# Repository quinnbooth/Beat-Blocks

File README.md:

# Beat-Blocks
Analog drum kit controlled by a sequencer. Theremin module for bassline.

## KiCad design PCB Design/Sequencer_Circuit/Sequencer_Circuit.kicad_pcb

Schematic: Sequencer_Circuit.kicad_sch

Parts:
5V_POWER1: Barrel_Jack_Switch; BARREL_JACK
555_TIMER1: LM555CN; DIP-8_W7.62mm
ALT_POWER1: Conn_01x02_Pin; OUTPUT_PINS_2
BEATS_1_1, BEATS_1_2, BEATS_1_3, BEATS_1_4, BEATS_2_1, BEATS_2_2, BEATS_2_3, BEATS_2_4, BEATS_3_1, BEATS_3_2, BEATS_3_3, BEATS_3_4: DM74LS54N
C1, C2, C3: C; C_Disc_D5.1mm_W3.2mm_P5.00mm
COMBINE_1, COMBINE_2, COMBINE_3: MC14012B
DISABLER1: GANGED_SW_SP3T; GANGED_SWITCH
D_1_1_1, D_1_1_2, D_1_2_1, D_1_2_2, D_1_3_1, D_1_3_2, D_1_4_1, D_1_4_2, D_1_5_1, D_1_5_2, D_1_6_1, D_1_6_2, D_1_7_1, D_1_7_2, D_1_8_1, D_1_8_2, D_2_1_1, D_2_1_2, D_2_2_1, D_2_2_2, D_2_3_1, D_2_3_2, D_2_4_1, D_2_4_2, D_2_5_1, D_2_5_2, D_2_6_1, D_2_6_2, D_2_7_1, D_2_7_2, D_2_8_1, D_2_8_2, D_3_1_1, D_3_1_2, D_3_2_1, D_3_2_2, D_3_3_1, D_3_3_2, D_3_4_1, D_3_4_2, D_3_5_1, D_3_5_2, D_3_6_1, D_3_6_2, D_3_7_1, D_3_7_2, D_3_8_1, D_3_8_2: LED; D_5W_P5.08mm_Vertical_AnodeUp
INVERT1: DM74LS04N
JK_1_1, JK_1_2, JK_1_3, JK_1_4, JK_1_5, JK_1_6, JK_1_7, JK_1_8, JK_2_1, JK_2_2, JK_2_3, JK_2_4, JK_2_5, JK_2_6, JK_2_7, JK_2_8, JK_3_1, JK_3_2, JK_3_3, JK_3_4, JK_3_5, JK_3_6, JK_3_7, JK_3_8: SN74107N; MPN SN74107N
ONE_SHOT1: SN74LS95BN
OUT_PINS1: OUT_PINS; OUTPUT_PINS_5
R1, R2: R; R_Axial_DIN0309_L9.0mm_D3.2mm_P12.70mm_Horizontal
R3: 1M; R_Axial_DIN0309_L9.0mm_D3.2mm_P12.70mm_Horizontal
R4: 100K; R_Axial_DIN0309_L9.0mm_D3.2mm_P12.70mm_Horizontal
R_1_1_1, R_1_1_2, R_1_2_1, R_1_2_2, R_1_3_1, R_1_3_2, R_1_4_1, R_1_4_2, R_1_5_1, R_1_5_2, R_1_6_1, R_1_6_2, R_1_7_1, R_1_7_2, R_1_8_1, R_1_8_2, R_2_1_1, R_2_1_2, R_2_2_1, R_2_2_2, R_2_3_1, R_2_3_2, R_2_4_1, R_2_4_2, R_2_5_1, R_2_5_2, R_2_6_1, R_2_6_2, R_2_7_1, R_2_7_2, R_2_8_1, R_2_8_2, R_3_1_1, R_3_1_2, R_3_2_1, R_3_2_2, R_3_3_1, R_3_3_2, R_3_4_1, R_3_4_2, R_3_5_1, R_3_5_2, R_3_6_1, R_3_6_2, R_3_7_1, R_3_7_2, R_3_8_1, R_3_8_2: R; R_Axial_DIN0309_L9.0mm_D3.2mm_P12.70mm_Horizontal
R_Tempo1: 2M; Potentiometer_Omeg_PC16BU_Vertical
SHIFT_1, SHIFT_2: DM74164N
SW1, SW2, SW3, SW4, SW5, SW6, SW7, SW8, SW9, SW10, SW11, SW12, SW13, SW14, SW15, SW16: ARCADE_BUTTON
SW1_C1, SW2_C1, SW3_C1, SW4_C1, SW5_C1, SW6_C1, SW7_C1, SW8_C1, SW9_C1, SW10_C1, SW11_C1, SW12_C1, SW13_C1, SW14_C1, SW15_C1, SW16_C1: C; C_Disc_D5.1mm_W3.2mm_P5.00mm
SW1_R1, SW1_R2, SW2_R1, SW2_R2, SW3_R1, SW3_R2, SW4_R1, SW4_R2, SW5_R1, SW5_R2, SW6_R1, SW6_R2, SW7_R1, SW7_R2, SW8_R1, SW8_R2, SW9_R1, SW9_R2, SW10_R1, SW10_R2, SW11_R1, SW11_R2, SW12_R1, SW12_R2, SW13_R1, SW13_R2, SW14_R1, SW14_R2, SW15_R1, SW15_R2, SW16_R1, SW16_R2: R; R_Axial_DIN0309_L9.0mm_D3.2mm_P12.70mm_Horizontal
XOR1: CD4070BE

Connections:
+5V: 5V_POWER1.1, 555_TIMER1.4 (R), 555_TIMER1.8 (VCC), ALT_POWER1.1, BEATS_1_1.5 (E), BEATS_1_1.9 (F), BEATS_1_1.14 (VCC), BEATS_1_2.5 (E), BEATS_1_2.9 (F), BEATS_1_2.14 (VCC), BEATS_1_3.5 (E), BEATS_1_3.9 (F), BEATS_1_3.14 (VCC), BEATS_1_4.5 (E), BEATS_1_4.9 (F), BEATS_1_4.14 (VCC), BEATS_2_1.5 (E), BEATS_2_1.9 (F), BEATS_2_1.14 (VCC), BEATS_2_2.5 (E), BEATS_2_2.9 (F), BEATS_2_2.14 (VCC), BEATS_2_3.5 (E), BEATS_2_3.9 (F), BEATS_2_3.14 (VCC), BEATS_2_4.5 (E), BEATS_2_4.9 (F), BEATS_2_4.14 (VCC), BEATS_3_1.5 (E), BEATS_3_1.9 (F), BEATS_3_1.14 (VCC), BEATS_3_2.5 (E), BEATS_3_2.9 (F), BEATS_3_2.14 (VCC), BEATS_3_3.5 (E), BEATS_3_3.9 (F), BEATS_3_3.14 (VCC), BEATS_3_4.5 (E), BEATS_3_4.9 (F), BEATS_3_4.14 (VCC), C3.1, COMBINE_1.11 (IN_3_B), COMBINE_1.12 (IN_4_B), COMBINE_1.14 (VDD), COMBINE_2.11 (IN_3_B), COMBINE_2.12 (IN_4_B), COMBINE_2.14 (VDD), COMBINE_3.11 (IN_3_B), COMBINE_3.12 (IN_4_B), COMBINE_3.14 (VDD), INVERT1.14 (VCC), JK_1_1.10 (2~CLR), JK_1_1.13 (1~CLR), JK_1_1.14 (VCC), JK_1_2.10 (2~CLR), JK_1_2.13 (1~CLR), JK_1_2.14 (VCC), JK_1_3.10 (2~CLR), JK_1_3.13 (1~CLR), JK_1_3.14 (VCC), JK_1_4.10 (2~CLR), JK_1_4.13 (1~CLR), JK_1_4.14 (VCC), JK_1_5.10 (2~CLR), JK_1_5.13 (1~CLR), JK_1_5.14 (VCC), JK_1_6.10 (2~CLR), JK_1_6.13 (1~CLR), JK_1_6.14 (VCC), JK_1_7.10 (2~CLR), JK_1_7.13 (1~CLR), JK_1_7.14 (VCC), JK_1_8.10 (2~CLR), JK_1_8.13 (1~CLR), JK_1_8.14 (VCC), JK_2_1.10 (2~CLR), JK_2_1.13 (1~CLR), JK_2_1.14 (VCC), JK_2_2.10 (2~CLR), JK_2_2.13 (1~CLR), JK_2_2.14 (VCC), JK_2_3.10 (2~CLR), JK_2_3.13 (1~CLR), JK_2_3.14 (VCC), JK_2_4.10 (2~CLR), JK_2_4.13 (1~CLR), JK_2_4.14 (VCC), JK_2_5.10 (2~CLR), JK_2_5.13 (1~CLR), JK_2_5.14 (VCC), JK_2_6.10 (2~CLR), JK_2_6.13 (1~CLR), JK_2_6.14 (VCC), JK_2_7.10 (2~CLR), JK_2_7.13 (1~CLR), JK_2_7.14 (VCC), JK_2_8.10 (2~CLR), JK_2_8.13 (1~CLR), JK_2_8.14 (VCC), JK_3_1.10 (2~CLR), JK_3_1.13 (1~CLR), JK_3_1.14 (VCC), JK_3_2.10 (2~CLR), JK_3_2.13 (1~CLR), JK_3_2.14 (VCC), JK_3_3.10 (2~CLR), JK_3_3.13 (1~CLR), JK_3_3.14 (VCC), JK_3_4.10 (2~CLR), JK_3_4.13 (1~CLR), JK_3_4.14 (VCC), JK_3_5.10 (2~CLR), JK_3_5.13 (1~CLR), JK_3_5.14 (VCC), JK_3_6.10 (2~CLR), JK_3_6.13 (1~CLR), JK_3_6.14 (VCC), JK_3_7.10 (2~CLR), JK_3_7.13 (1~CLR), JK_3_7.14 (VCC), JK_3_8.10 (2~CLR), JK_3_8.13 (1~CLR), JK_3_8.14 (VCC), ONE_SHOT1.14 (VCC), R2.1, R3.2, SHIFT_1.2 (B), SHIFT_1.9 (CLR), SHIFT_1.14 (VCC), SHIFT_2.2 (B), SHIFT_2.9 (CLR), SHIFT_2.14 (VCC), SW1_R2.1, SW2_R2.2, SW3_R2.1, SW4_R2.2, SW5_R2.1, SW6_R2.2, SW7_R2.1, SW8_R2.2, SW9_R2.1, SW10_R2.2, SW11_R2.1, SW12_R2.2, SW13_R2.1, SW14_R2.2, SW15_R2.1, SW16_R2.2, XOR1.14 (VDD)
GND: 5V_POWER1.2, 5V_POWER1.3, 555_TIMER1.1 (GND), ALT_POWER1.2, BEATS_1_1.7 (GND), BEATS_1_2.7 (GND), BEATS_1_3.7 (GND), BEATS_1_4.7 (GND), BEATS_2_1.7 (GND), BEATS_2_2.7 (GND), BEATS_2_3.7 (GND), BEATS_2_4.7 (GND), BEATS_3_1.7 (GND), BEATS_3_2.7 (GND), BEATS_3_3.7 (GND), BEATS_3_4.7 (GND), C1.1, C2.2, C3.2, COMBINE_1.7 (VSS), COMBINE_2.7 (VSS), COMBINE_3.7 (VSS), DISABLER1.7, DISABLER1.8 (7), INVERT1.7 (GND), JK_1_1.7 (GND), JK_1_2.7 (GND), JK_1_3.7 (GND), JK_1_4.7 (GND), JK_1_5.7 (GND), JK_1_6.7 (GND), JK_1_7.7 (GND), JK_1_8.7 (GND), JK_2_1.7 (GND), JK_2_2.7 (GND), JK_2_3.7 (GND), JK_2_4.7 (GND), JK_2_5.7 (GND), JK_2_6.7 (GND), JK_2_7.7 (GND), JK_2_8.7 (GND), JK_3_1.7 (GND), JK_3_2.7 (GND), JK_3_3.7 (GND), JK_3_4.7 (GND), JK_3_5.7 (GND), JK_3_6.7 (GND), JK_3_7.7 (GND), JK_3_8.7 (GND), ONE_SHOT1.1 (SER), ONE_SHOT1.6 (MODE), ONE_SHOT1.7 (GND), OUT_PINS1.1, R4.2, R_1_1_1.1, R_1_1_2.1, R_1_2_1.1, R_1_2_2.1, R_1_3_1.1, R_1_3_2.1, R_1_4_1.1, R_1_4_2.1, R_1_5_1.1, R_1_5_2.1, R_1_6_1.1, R_1_6_2.1, R_1_7_1.1, R_1_7_2.1, R_1_8_1.1, R_1_8_2.1, R_2_1_1.1, R_2_1_2.1, R_2_2_1.1, R_2_2_2.1, R_2_3_1.1, R_2_3_2.1, R_2_4_1.1, R_2_4_2.1, R_2_5_1.1, R_2_5_2.1, R_2_6_1.1, R_2_6_2.1, R_2_7_1.1, R_2_7_2.1, R_2_8_1.1, R_2_8_2.1, R_3_1_1.1, R_3_1_2.1, R_3_2_1.1, R_3_2_2.1, R_3_3_1.1, R_3_3_2.1, R_3_4_1.1, R_3_4_2.1, R_3_5_1.1, R_3_5_2.1, R_3_6_1.1, R_3_6_2.1, R_3_7_1.1, R_3_7_2.1, R_3_8_1.1, R_3_8_2.1, SHIFT_1.7 (GND), SHIFT_2.7 (GND), SW1.2, SW1_C1.2, SW1_R1.1, SW2.2, SW2_C1.2, SW2_R1.1, SW3.2, SW3_C1.2, SW3_R1.1, SW4.2, SW4_C1.2, SW4_R1.1, SW5.2, SW5_C1.2, SW5_R1.1, SW6.2, SW6_C1.2, SW6_R1.1, SW7.2, SW7_C1.2, SW7_R1.1, SW8.2, SW8_C1.2, SW8_R1.1, SW9.2, SW9_C1.2, SW9_R1.1, SW10.2, SW10_C1.2, SW10_R1.1, SW11.2, SW11_C1.2, SW11_R1.1, SW12.2, SW12_C1.2, SW12_R1.1, SW13.2, SW13_C1.2, SW13_R1.1, SW14.2, SW14_C1.2, SW14_R1.1, SW15.2, SW15_C1.2, SW15_R1.1, SW16.2, SW16_C1.2, SW16_R1.1, XOR1.5 (C), XOR1.7 (GND)
unnamed: 555_TIMER1.5 (CV), C1.2
unnamed: 555_TIMER1.7 (DIS), R1.2, R2.2
unnamed: 555_TIMER1.3 (Q), COMBINE_1.9 (IN_1_B), COMBINE_2.9 (IN_1_B), COMBINE_3.9 (IN_1_B), ONE_SHOT1.9 (CLK1), SHIFT_1.8 (CLK), SHIFT_2.8 (CLK)
unnamed: 555_TIMER1.2 (TR), 555_TIMER1.6 (THR), C2.1, R_Tempo1.1, R_Tempo1.2
unnamed: BEATS_1_1.1 (A), D_1_1_1.2 (A), JK_1_1.3 (1Q)
unnamed: BEATS_1_1.2 (B), BEATS_2_1.2 (B), BEATS_3_1.2 (B), SHIFT_1.3 (Q_A), SW1.3
unnamed: BEATS_1_1.3 (C), D_1_1_2.2 (A), JK_1_1.5 (2Q)
unnamed: BEATS_1_1.4 (D), BEATS_2_1.4 (D), BEATS_3_1.4 (D), SHIFT_1.4 (Q_B), SW2.3
unnamed: BEATS_1_1.10 (G), BEATS_2_1.10 (G), BEATS_3_1.10 (G), SHIFT_1.6 (Q_D), SW4.3
unnamed: BEATS_1_1.11 (H), D_1_2_2.2 (A), JK_1_2.5 (2Q)
unnamed: BEATS_1_1.12 (I), BEATS_2_1.12 (I), BEATS_3_1.12 (I), SHIFT_1.5 (Q_C), SW3.3
unnamed: BEATS_1_1.13 (J), D_1_2_1.2 (A), JK_1_2.3 (1Q)
unnamed: BEATS_1_1.6 (Y), COMBINE_1.2 (IN_1_A)
unnamed: BEATS_1_2.1 (A), D_1_3_1.2 (A), JK_1_3.3 (1Q)
unnamed: BEATS_1_2.2 (B), BEATS_2_2.2 (B), BEATS_3_2.2 (B), SHIFT_1.10 (Q_E), SW5.3
unnamed: BEATS_1_2.3 (C), D_1_3_2.2 (A), JK_1_3.5 (2Q)
unnamed: BEATS_1_2.4 (D), BEATS_2_2.4 (D), BEATS_3_2.4 (D), SHIFT_1.11 (Q_F), SW6.3
unnamed: BEATS_1_2.10 (G), BEATS_2_2.10 (G), BEATS_3_2.10 (G), SHIFT_1.13 (Q_H), SW8.3, XOR1.6 (D)
unnamed: BEATS_1_2.11 (H), D_1_4_2.2 (A), JK_1_4.5 (2Q)
unnamed: BEATS_1_2.12 (I), BEATS_2_2.12 (I), BEATS_3_2.12 (I), SHIFT_1.12 (Q_G), SW7.3
unnamed: BEATS_1_2.13 (J), D_1_4_1.2 (A), JK_1_4.3 (1Q)
unnamed: BEATS_1_2.6 (Y), COMBINE_1.3 (IN_2_A)
unnamed: BEATS_1_3.1 (A), D_1_5_1.2 (A), JK_1_5.3 (1Q)
unnamed: BEATS_1_3.2 (B), BEATS_2_3.2 (B), BEATS_3_3.2 (B), SHIFT_2.3 (Q_A), SW9.3
unnamed: BEATS_1_3.3 (C), D_1_5_2.2 (A), JK_1_5.5 (2Q)
unnamed: BEATS_1_3.4 (D), BEATS_2_3.4 (D), BEATS_3_3.4 (D), SHIFT_2.4 (Q_B), SW10.3
unnamed: BEATS_1_3.10 (G), BEATS_2_3.10 (G), BEATS_3_3.10 (G), SHIFT_2.6 (Q_D), SW12.3
unnamed: BEATS_1_3.11 (H), D_1_6_2.2 (A), JK_1_6.5 (2Q)
unnamed: BEATS_1_3.12 (I), BEATS_2_3.12 (I), BEATS_3_3.12 (I), SHIFT_2.5 (Q_C), SW11.3
unnamed: BEATS_1_3.13 (J), D_1_6_1.2 (A), JK_1_6.3 (1Q)
unnamed: BEATS_1_3.6 (Y), COMBINE_1.4 (IN_3_A)
unnamed: BEATS_1_4.1 (A), D_1_7_1.2 (A), JK_1_7.3 (1Q)
unnamed: BEATS_1_4.2 (B), BEATS_2_4.2 (B), BEATS_3_4.2 (B), SHIFT_2.10 (Q_E), SW13.3
unnamed: BEATS_1_4.3 (C), D_1_7_2.2 (A), JK_1_7.5 (2Q)
unnamed: BEATS_1_4.4 (D), BEATS_2_4.4 (D), BEATS_3_4.4 (D), SHIFT_2.11 (Q_F), SW14.3
unnamed: BEATS_1_4.10 (G), BEATS_2_4.10 (G), BEATS_3_4.10 (G), SHIFT_2.13 (Q_H), SW16.3, XOR1.13 (H)
unnamed: BEATS_1_4.11 (H), D_1_8_2.2 (A), JK_1_8.5 (2Q)
unnamed: BEATS_1_4.12 (I), BEATS_2_4.12 (I), BEATS_3_4.12 (I), SHIFT_2.12 (Q_G), SW15.3
unnamed: BEATS_1_4.13 (J), D_1_8_1.2 (A), JK_1_8.3 (1Q)
unnamed: BEATS_1_4.6 (Y), COMBINE_1.5 (IN_4_A)
unnamed: BEATS_2_1.1 (A), D_2_1_1.2 (A), JK_2_1.3 (1Q)
unnamed: BEATS_2_1.3 (C), D_2_1_2.2 (A), JK_2_1.5 (2Q)
unnamed: BEATS_2_1.11 (H), D_2_2_2.2 (A), JK_2_2.5 (2Q)
unnamed: BEATS_2_1.13 (J), D_2_2_1.2 (A), JK_2_2.3 (1Q)
unnamed: BEATS_2_1.6 (Y), COMBINE_2.2 (IN_1_A)
unnamed: BEATS_2_2.1 (A), D_2_3_1.2 (A), JK_2_3.3 (1Q)
unnamed: BEATS_2_2.3 (C), D_2_3_2.2 (A), JK_2_3.5 (2Q)
unnamed: BEATS_2_2.11 (H), D_2_4_2.2 (A), JK_2_4.5 (2Q)
unnamed: BEATS_2_2.13 (J), D_2_4_1.2 (A), JK_2_4.3 (1Q)
unnamed: BEATS_2_2.6 (Y), COMBINE_2.3 (IN_2_A)
unnamed: BEATS_2_3.1 (A), D_2_5_1.2 (A), JK_2_5.3 (1Q)
unnamed: BEATS_2_3.3 (C), D_2_5_2.2 (A), JK_2_5.5 (2Q)
unnamed: BEATS_2_3.11 (H), D_2_6_2.2 (A), JK_2_6.5 (2Q)
unnamed: BEATS_2_3.13 (J), D_2_6_1.2 (A), JK_2_6.3 (1Q)
unnamed: BEATS_2_3.6 (Y), COMBINE_2.4 (IN_3_A)
unnamed: BEATS_2_4.1 (A), D_2_7_1.2 (A), JK_2_7.3 (1Q)
unnamed: BEATS_2_4.3 (C), D_2_7_2.2 (A), JK_2_7.5 (2Q)
unnamed: BEATS_2_4.11 (H), D_2_8_2.2 (A), JK_2_8.5 (2Q)
unnamed: BEATS_2_4.13 (J), D_2_8_1.2 (A), JK_2_8.3 (1Q)
unnamed: BEATS_2_4.6 (Y), COMBINE_2.5 (IN_4_A)
unnamed: BEATS_3_1.1 (A), D_3_1_1.2 (A), JK_3_1.3 (1Q)
unnamed: BEATS_3_1.3 (C), D_3_1_2.2 (A), JK_3_1.5 (2Q)
unnamed: BEATS_3_1.11 (H), D_3_2_2.2 (A), JK_3_2.5 (2Q)
unnamed: BEATS_3_1.13 (J), D_3_2_1.2 (A), JK_3_2.3 (1Q)
unnamed: BEATS_3_1.6 (Y), COMBINE_3.2 (IN_1_A)
unnamed: BEATS_3_2.1 (A), D_3_3_1.2 (A), JK_3_3.3 (1Q)
unnamed: BEATS_3_2.3 (C), D_3_3_2.2 (A), JK_3_3.5 (2Q)
unnamed: BEATS_3_2.11 (H), D_3_4_2.2 (A), JK_3_4.5 (2Q)
unnamed: BEATS_3_2.13 (J), D_3_4_1.2 (A), JK_3_4.3 (1Q)
unnamed: BEATS_3_2.6 (Y), COMBINE_3.3 (IN_2_A)
unnamed: BEATS_3_3.1 (A), D_3_5_1.2 (A), JK_3_5.3 (1Q)
unnamed: BEATS_3_3.3 (C), D_3_5_2.2 (A), JK_3_5.5 (2Q)
unnamed: BEATS_3_3.11 (H), D_3_6_2.2 (A), JK_3_6.5 (2Q)
unnamed: BEATS_3_3.13 (J), D_3_6_1.2 (A), JK_3_6.3 (1Q)
unnamed: BEATS_3_3.6 (Y), COMBINE_3.4 (IN_3_A)
unnamed: BEATS_3_4.1 (A), D_3_7_1.2 (A), JK_3_7.3 (1Q)
unnamed: BEATS_3_4.3 (C), D_3_7_2.2 (A), JK_3_7.5 (2Q)
unnamed: BEATS_3_4.11 (H), D_3_8_2.2 (A), JK_3_8.5 (2Q)
unnamed: BEATS_3_4.13 (J), D_3_8_1.2 (A), JK_3_8.3 (1Q)
unnamed: BEATS_3_4.6 (Y), COMBINE_3.5 (IN_4_A)
unnamed: COMBINE_1.1 (OUT_A), COMBINE_1.10 (IN_2_B)
unnamed: COMBINE_1.13 (OUT_B), INVERT1.1 (A1)
unnamed: COMBINE_2.1 (OUT_A), COMBINE_2.10 (IN_2_B)
unnamed: COMBINE_2.13 (OUT_B), INVERT1.3 (A2)
unnamed: COMBINE_3.1 (OUT_A), COMBINE_3.10 (IN_2_B)
unnamed: COMBINE_3.13 (OUT_B), INVERT1.5 (A3)
unnamed: D_1_1_1.1 (K), R_1_1_1.2
unnamed: D_1_1_2.1 (K), R_1_1_2.2
unnamed: D_1_2_1.1 (K), R_1_2_1.2
unnamed: D_1_2_2.1 (K), R_1_2_2.2
unnamed: D_1_3_1.1 (K), R_1_3_1.2
unnamed: D_1_3_2.1 (K), R_1_3_2.2
unnamed: D_1_4_1.1 (K), R_1_4_1.2
unnamed: D_1_4_2.1 (K), R_1_4_2.2
unnamed: D_1_5_1.1 (K), R_1_5_1.2
unnamed: D_1_5_2.1 (K), R_1_5_2.2
unnamed: D_1_6_1.1 (K), R_1_6_1.2
unnamed: D_1_6_2.1 (K), R_1_6_2.2
unnamed: D_1_7_1.1 (K), R_1_7_1.2
unnamed: D_1_7_2.1 (K), R_1_7_2.2
unnamed: D_1_8_1.1 (K), R_1_8_1.2
unnamed: D_1_8_2.1 (K), R_1_8_2.2
unnamed: D_2_1_1.1 (K), R_2_1_1.2
unnamed: D_2_1_2.1 (K), R_2_1_2.2
unnamed: D_2_2_1.1 (K), R_2_2_1.2
unnamed: D_2_2_2.1 (K), R_2_2_2.2
unnamed: D_2_3_1.1 (K), R_2_3_1.2
unnamed: D_2_3_2.1 (K), R_2_3_2.2
unnamed: D_2_4_1.1 (K), R_2_4_1.2
unnamed: D_2_4_2.1 (K), R_2_4_2.2
unnamed: D_2_5_1.1 (K), R_2_5_1.2
unnamed: D_2_5_2.1 (K), R_2_5_2.2
unnamed: D_2_6_1.1 (K), R_2_6_1.2
unnamed: D_2_6_2.1 (K), R_2_6_2.2
unnamed: D_2_7_1.1 (K), R_2_7_1.2
unnamed: D_2_7_2.1 (K), R_2_7_2.2
unnamed: D_2_8_1.1 (K), R_2_8_1.2
unnamed: D_2_8_2.1 (K), R_2_8_2.2
unnamed: D_3_1_1.1 (K), R_3_1_1.2
unnamed: D_3_1_2.1 (K), R_3_1_2.2
unnamed: D_3_2_1.1 (K), R_3_2_1.2
unnamed: D_3_2_2.1 (K), R_3_2_2.2
unnamed: D_3_3_1.1 (K), R_3_3_1.2
unnamed: D_3_3_2.1 (K), R_3_3_2.2
unnamed: D_3_4_1.1 (K), R_3_4_1.2
unnamed: D_3_4_2.1 (K), R_3_4_2.2
unnamed: D_3_5_1.1 (K), R_3_5_1.2
unnamed: D_3_5_2.1 (K), R_3_5_2.2
unnamed: D_3_6_1.1 (K), R_3_6_1.2
unnamed: D_3_6_2.1 (K), R_3_6_2.2
unnamed: D_3_7_1.1 (K), R_3_7_1.2
unnamed: D_3_7_2.1 (K), R_3_7_2.2
unnamed: D_3_8_1.1 (K), R_3_8_1.2
unnamed: D_3_8_2.1 (K), R_3_8_2.2
unnamed: INVERT1.2 (Y1), OUT_PINS1.3
unnamed: INVERT1.4 (Y2), OUT_PINS1.4
unnamed: INVERT1.6 (Y3), OUT_PINS1.5
unnamed: JK_1_1.12 (1CLK), JK_2_1.12 (1CLK), JK_3_1.12 (1CLK), SW1.1, SW1_C1.1, SW1_R2.2
unnamed: DISABLER1.4, DISABLER1.5, JK_1_1.1 (1J), JK_1_1.4 (1K), JK_1_1.8 (2J), JK_1_1.11 (2K), JK_1_2.1 (1J), JK_1_2.4 (1K), JK_1_2.8 (2J), JK_1_2.11 (2K), JK_1_3.1 (1J), JK_1_3.4 (1K), JK_1_3.8 (2J), JK_1_3.11 (2K), JK_1_4.1 (1J), JK_1_4.4 (1K), JK_1_4.8 (2J), JK_1_4.11 (2K), JK_1_5.1 (1J), JK_1_5.4 (1K), JK_1_5.8 (2J), JK_1_5.11 (2K), JK_1_6.1 (1J), JK_1_6.4 (1K), JK_1_6.8 (2J), JK_1_6.11 (2K), JK_1_7.1 (1J), JK_1_7.4 (1K), JK_1_7.8 (2J), JK_1_7.11 (2K), JK_1_8.1 (1J), JK_1_8.4 (1K), JK_1_8.8 (2J), JK_1_8.11 (2K)
unnamed: JK_1_1.9 (2CLK), JK_2_1.9 (2CLK), JK_3_1.9 (2CLK), SW2.1, SW2_C1.1, SW2_R2.1
unnamed: JK_1_2.12 (1CLK), JK_2_2.12 (1CLK), JK_3_2.12 (1CLK), SW3.1, SW3_C1.1, SW3_R2.2
unnamed: JK_1_2.9 (2CLK), JK_2_2.9 (2CLK), JK_3_2.9 (2CLK), SW4.1, SW4_C1.1, SW4_R2.1
unnamed: JK_1_3.12 (1CLK), JK_2_3.12 (1CLK), JK_3_3.12 (1CLK), SW5.1, SW5_C1.1, SW5_R2.2
unnamed: JK_1_3.9 (2CLK), JK_2_3.9 (2CLK), JK_3_3.9 (2CLK), SW6.1, SW6_C1.1, SW6_R2.1
unnamed: JK_1_4.12 (1CLK), JK_2_4.12 (1CLK), JK_3_4.12 (1CLK), SW7.1, SW7_C1.1, SW7_R2.2
unnamed: JK_1_4.9 (2CLK), JK_2_4.9 (2CLK), JK_3_4.9 (2CLK), SW8.1, SW8_C1.1, SW8_R2.1
unnamed: JK_1_5.12 (1CLK), JK_2_5.12 (1CLK), JK_3_5.12 (1CLK), SW9.1, SW9_C1.1, SW9_R2.2
unnamed: JK_1_5.9 (2CLK), JK_2_5.9 (2CLK), JK_3_5.9 (2CLK), SW10.1, SW10_C1.1, SW10_R2.1
unnamed: JK_1_6.12 (1CLK), JK_2_6.12 (1CLK), JK_3_6.12 (1CLK), SW11.1, SW11_C1.1, SW11_R2.2
unnamed: JK_1_6.9 (2CLK), JK_2_6.9 (2CLK), JK_3_6.9 (2CLK), SW12.1, SW12_C1.1, SW12_R2.1
unnamed: JK_1_7.12 (1CLK), JK_2_7.12 (1CLK), JK_3_7.12 (1CLK), SW13.1, SW13_C1.1, SW13_R2.2
unnamed: JK_1_7.9 (2CLK), JK_2_7.9 (2CLK), JK_3_7.9 (2CLK), SW14.1, SW14_C1.1, SW14_R2.1
unnamed: JK_1_8.12 (1CLK), JK_2_8.12 (1CLK), JK_3_8.12 (1CLK), SW15.1, SW15_C1.1, SW15_R2.2
unnamed: JK_1_8.9 (2CLK), JK_2_8.9 (2CLK), JK_3_8.9 (2CLK), SW16.1, SW16_C1.1, SW16_R2.1
unnamed: DISABLER1.1, DISABLER1.6, JK_2_1.1 (1J), JK_2_1.4 (1K), JK_2_1.8 (2J), JK_2_1.11 (2K), JK_2_2.1 (1J), JK_2_2.4 (1K), JK_2_2.8 (2J), JK_2_2.11 (2K), JK_2_3.1 (1J), JK_2_3.4 (1K), JK_2_3.8 (2J), JK_2_3.11 (2K), JK_2_4.1 (1J), JK_2_4.4 (1K), JK_2_4.8 (2J), JK_2_4.11 (2K), JK_2_5.1 (1J), JK_2_5.4 (1K), JK_2_5.8 (2J), JK_2_5.11 (2K), JK_2_6.1 (1J), JK_2_6.4 (1K), JK_2_6.8 (2J), JK_2_6.11 (2K), JK_2_7.1 (1J), JK_2_7.4 (1K), JK_2_7.8 (2J), JK_2_7.11 (2K), JK_2_8.1 (1J), JK_2_8.4 (1K), JK_2_8.8 (2J), JK_2_8.11 (2K)
unnamed: DISABLER1.2, DISABLER1.3, JK_3_1.1 (1J), JK_3_1.4 (1K), JK_3_1.8 (2J), JK_3_1.11 (2K), JK_3_2.1 (1J), JK_3_2.4 (1K), JK_3_2.8 (2J), JK_3_2.11 (2K), JK_3_3.1 (1J), JK_3_3.4 (1K), JK_3_3.8 (2J), JK_3_3.11 (2K), JK_3_4.1 (1J), JK_3_4.4 (1K), JK_3_4.8 (2J), JK_3_4.11 (2K), JK_3_5.1 (1J), JK_3_5.4 (1K), JK_3_5.8 (2J), JK_3_5.11 (2K), JK_3_6.1 (1J), JK_3_6.4 (1K), JK_3_6.8 (2J), JK_3_6.11 (2K), JK_3_7.1 (1J), JK_3_7.4 (1K), JK_3_7.8 (2J), JK_3_7.11 (2K), JK_3_8.1 (1J), JK_3_8.4 (1K), JK_3_8.8 (2J), JK_3_8.11 (2K)
unnamed: ONE_SHOT1.13 (Q_A), XOR1.9 (F)
unnamed: ONE_SHOT1.12 (Q_B), XOR1.8 (E)
unnamed: OUT_PINS1.2, R3.1, R4.1
unnamed: R1.1, R_Tempo1.3
unnamed: SHIFT_1.1 (A), XOR1.11 (M)
unnamed: SHIFT_2.1 (A), XOR1.4 (K)
unnamed: SW1.4, SW1_R1.2
unnamed: SW2.4, SW2_R1.2
unnamed: SW3.4, SW3_R1.2
unnamed: SW4.4, SW4_R1.2
unnamed: SW5.4, SW5_R1.2
unnamed: SW6.4, SW6_R1.2
unnamed: SW7.4, SW7_R1.2
unnamed: SW8.4, SW8_R1.2
unnamed: SW9.4, SW9_R1.2
unnamed: SW10.4, SW10_R1.2
unnamed: SW11.4, SW11_R1.2
unnamed: SW12.4, SW12_R1.2
unnamed: SW13.4, SW13_R1.2
unnamed: SW14.4, SW14_R1.2
unnamed: SW15.4, SW15_R1.2
unnamed: SW16.4, SW16_R1.2
unnamed: XOR1.10 (L), XOR1.12 (G)

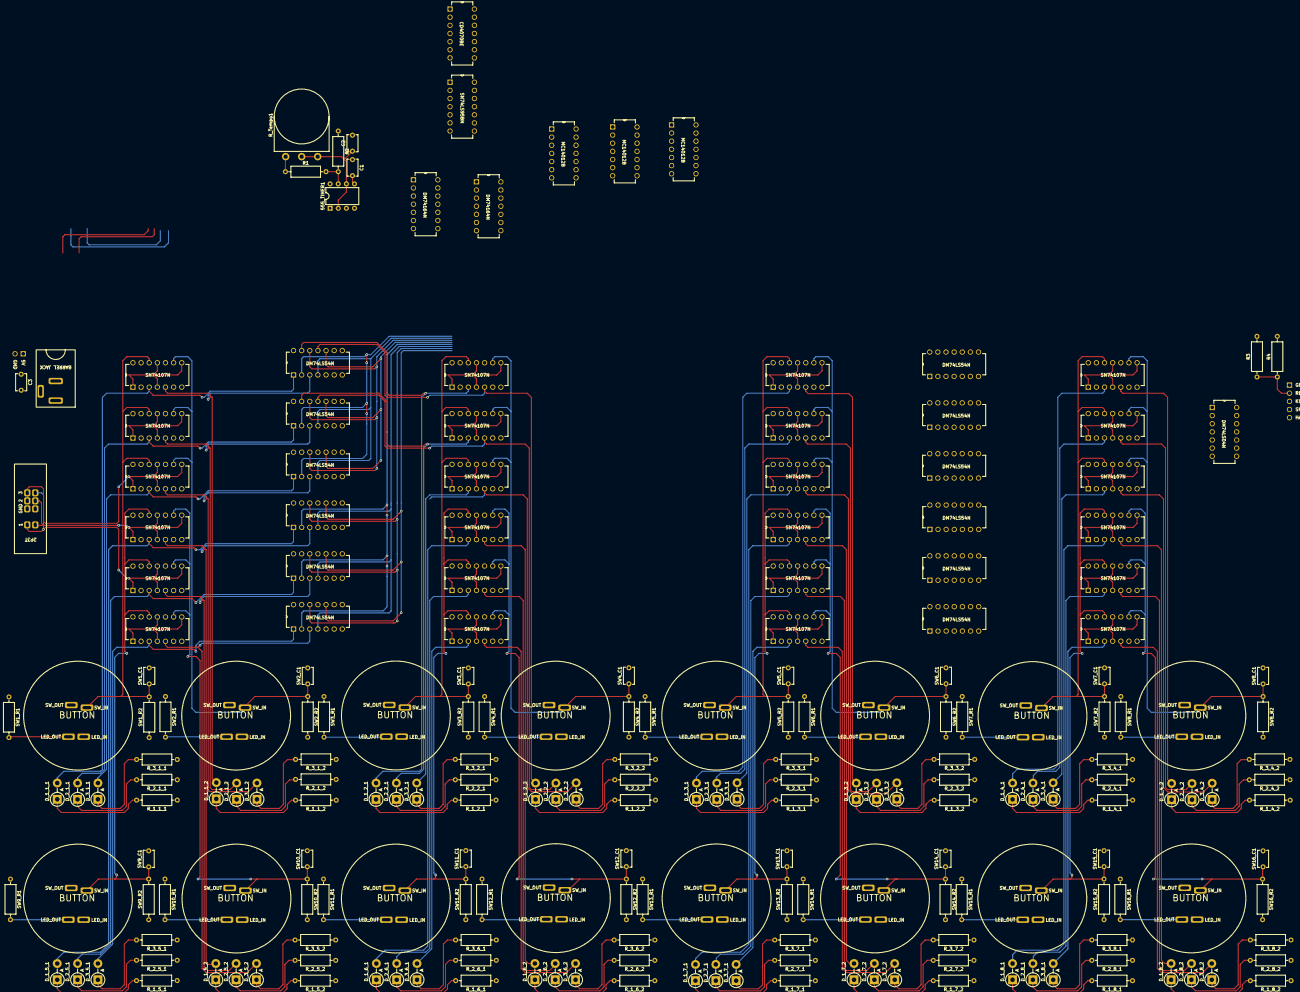
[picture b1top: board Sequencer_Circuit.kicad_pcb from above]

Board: 2 copper layers, 217 parts (0 on the bottom side), 181 nets.

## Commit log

2024-03-06 Start sequencer schematic
2024-03-06 Sequencer update
2024-03-07 Sequencer complete schematic w/o values
2024-03-10 Initial sequencer PCB
2024-03-11 Sequencer PCB
